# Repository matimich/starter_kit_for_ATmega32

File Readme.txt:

Author:Mateusz Michalski
Program: EAGLE

The aim of the project was to create starter kit for ATmega32.

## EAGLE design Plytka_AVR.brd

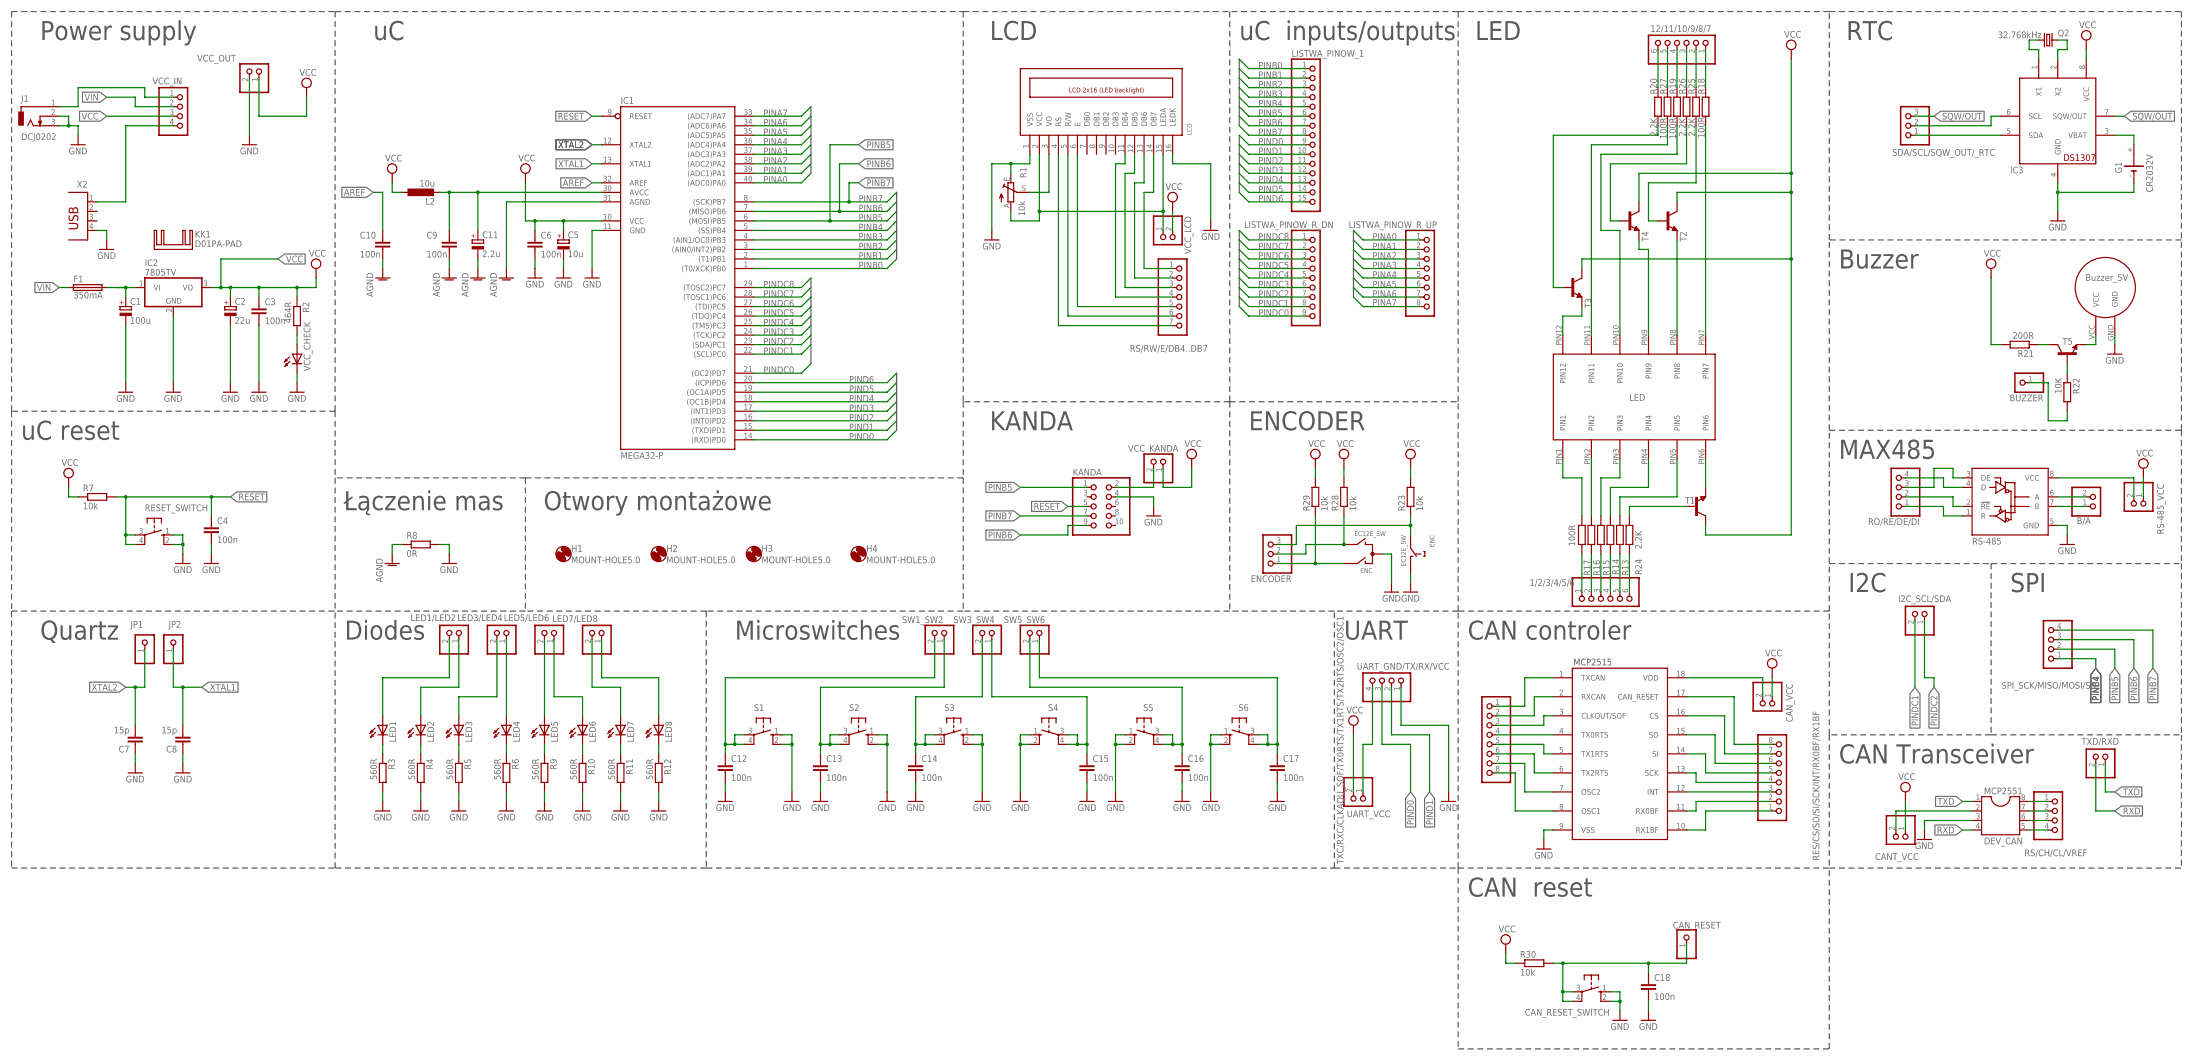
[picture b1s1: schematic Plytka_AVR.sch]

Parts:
1/2/3/4/5/6, 12/11/10/9/8/7: PINHD-1X6; 1X06
B/A: PINHD-1X2; 1X02
BUZZER: PINHD-1X1; 1X01
C1: 100u; E2,5-6
C2: 22u; E2,5-6
C3, C4, C6, C9, C10, C12, C13, C14, C15, C16, C17, C18: 100n; C050-024X044
C5: 10u; E2,5-6
C7, C8: 15p; C050-024X044
C11: 2.2u; E2,5-6
CANT_VCC: PINHD-1X2; 1X02
CAN_RESET: PINHD-1X1; 1X01
CAN_RESET_SWITCH: 10-XX; B3F-10XX
CAN_VCC: PINHD-1X2; 1X02
ENC: EC12E_SW; ALPS_EC12E_SW
ENCODER: PINHD-1X3; 1X03
F1: 350mA; SHK20L
G1: CR2032V
H1, H2, H3, H4: MOUNT-HOLE5.0; 5,0
I2C_SCL/SDA: PINHD-1X2; 1X02
IC1: MEGA32-P; DIL40
IC2: 7805TV; TO220V
IC3: DS1307; DIL08
J1: DCJ0202
JP1, JP2: PINHD-1X1; 1X01
KANDA: PINHD-2X5; 2X05
KK1: D01PA-PAD
L2: 10u; 0204/7
LCD: LCD_2X16_SIL; HY-1602F
LED1, LED2, LED3, LED4, LED5, LED6, LED7, LED8: LED5MM
LED1/LED2, LED3/LED4, LED5/LED6, LED7/LED8: PINHD-1X2; 1X02
LISTWA_PINOW_1: PINHD-1X15; 1X15
LISTWA_PINOW_R_DN: PINHD-1X9; 1X09
LISTWA_PINOW_R_UP: PINHD-1X8MAT8; 1X08
MCP2551: DEV_CAN; DIL08
Q2: 32.768kHz; TC26V
R1: 10k; CA6V
R2: 464R; 0204/7
R3, R4, R5, R6, R9, R10, R11, R12: 560R; 0204/7
R7, R23, R28, R29, R30: 10k; 0204/7
R8: 0R; 0204/7
R13, R14, R15, R16, R17, R18, R19, R27: 100R; 0204/7
R20, R24, R25, R26: 2.2K; 0204/7
R21: 200R; 0204/7
R22: 10K; 0204/7
RES/CS/SO/SI/SCK/INT/RX0BF/RX1BF: PINHD-1X8; 1X08
RESET_SWITCH: 10-XX; B3F-10XX
RO/RE/DE/DI: PINHD-1X4; 1X04
RS-485: RS-485; DIL08
RS-485_VCC: PINHD-1X2; 1X02
RS/CH/CL/VREF: PINHD-1X4; 1X04
RS/RW/E/DB4..DB7: PINHD-1X7MAT_LCD; 1X07
S1, S2, S3, S4, S5, S6: 10-XX; B3F-10XX
SDA/SCL/SQW_OUT/_RTC: PINHD-1X3; 1X03
SPI_SCK/MISO/MOSI/SS: PINHD-1X4; 1X04
SW1_SW2, SW3_SW4, SW5_SW6: PINHD-1X2; 1X02
T1, T2, T3, T4, T5: -NPN-TO92; TO92
TXC/RXC/CLKAOU_SOF/TX0RTS/TX1RTS/TX2RTS/OSC2/OSC1: PINHD-1X8; 1X08
TXD/RXD: PINHD-1X2; 1X02
U$1: LED_MAT; LED_MOJ
U$2: BUZZER_MAT
U$3: MCP2515; DIP18
UART_GND/TX/RX/VCC: PINHD-1X4; 1X04
UART_VCC: PINHD-1X2; 1X02
VCC_CHECK: LED5MM
VCC_IN: PINHD-1X4; 1X04
VCC_KANDA: PINHD-1X2; 1X02
VCC_LCD: PINHD-1X2; 1X02
VCC_OUT: PINHD-1X2; 1X02
X2: PN87520

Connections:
AGND: C9.2, C10.2, C11.-, IC1.31 (AGND), R8.1
AREF: C10.1, IC1.32 (AREF)
DB4: LCD.11 (DB4), RS/RW/E/DB4..DB7.4
DB5: LCD.12 (DB5), RS/RW/E/DB4..DB7.3
DB6: LCD.13 (DB6), RS/RW/E/DB4..DB7.2
DB7: LCD.14 (DB7), RS/RW/E/DB4..DB7.1
E: LCD.6 (E), RS/RW/E/DB4..DB7.5
GND: C1.-, C2.-, C3.2, C4.2, C5.-, C6.2, C7.1, C8.1, C12.2, C13.2, C14.2, C15.2, C16.2, C17.2, C18.2, CAN_RESET_SWITCH.1 (S), CAN_RESET_SWITCH.2 (S1), ENC.C, ENC.D (1), G1.-, IC1.11 (GND), IC2.2 (GND), IC3.4 (GND), J1.2, J1.3, KANDA.4, LCD.1 (VSS), LCD.16 (LEDK), MCP2551.3 (VDD), R1.E, R3.2, R4.2, R5.2, R6.2, R8.2, R9.2, R10.2, R11.2, R12.2, RESET_SWITCH.1 (S), RESET_SWITCH.2 (S1), RS-485.5 (GND), S1.1 (S), S1.2 (S1), S2.1 (S), S2.2 (S1), S3.1 (S), S3.2 (S1), S4.1 (S), S4.2 (S1), S5.1 (S), S5.2 (S1), S6.1 (S), S6.2 (S1), U$2.GND, U$3.9 (VSS), UART_GND/TX/RX/VCC.1, VCC_CHECK.K (C), VCC_OUT.2 (1), X2.4
unnamed: J1.1, VCC_IN.1
unnamed: VCC_IN.4, X2.1
unnamed: T1.1 (E), U$1.PIN6
unnamed: R2.2, VCC_CHECK.A
unnamed: C9.1, C11.+, IC1.30 (AVCC), L2.2
unnamed: MCP2551.8 (RS), RS/CH/CL/VREF.1
unnamed: 12/11/10/9/8/7.6 (1), R20.1
unnamed: 1/2/3/4/5/6.1 (6), R17.2
unnamed: 1/2/3/4/5/6.2 (5), R16.2
unnamed: 1/2/3/4/5/6.3 (4), R15.2
unnamed: 1/2/3/4/5/6.4 (3), R14.2
unnamed: 1/2/3/4/5/6.5 (2), R13.2
unnamed: R17.1, U$1.PIN1
unnamed: R27.1, U$1.PIN11
unnamed: LED1.K (C), R3.1
unnamed: LED1.A, LED1/LED2.2 (1)
unnamed: 12/11/10/9/8/7.4 (3), R19.2
unnamed: R18.1, U$1.PIN7
unnamed: R16.1, U$1.PIN2
unnamed: R15.1, U$1.PIN3
unnamed: R14.1, U$1.PIN4
unnamed: R13.1, U$1.PIN5
unnamed: 12/11/10/9/8/7.1 (6), R18.2
unnamed: 12/11/10/9/8/7.2 (5), R25.1
unnamed: T2.1 (E), U$1.PIN8
unnamed: 1/2/3/4/5/6.6 (1), R24.1
unnamed: LED1/LED2.1 (2), LED2.A
unnamed: LED3.A, LED3/LED4.2 (1)
unnamed: LED5/LED6.1 (2), LED6.A
unnamed: LED5.K (C), R9.1
unnamed: LED2.K (C), R4.1
unnamed: LED6.K (C), R10.1
unnamed: LED3.K (C), R5.1
unnamed: LED7.K (C), R11.1
unnamed: LED4.K (C), R6.1
unnamed: LED8.K (C), R12.1
unnamed: LED5.A, LED5/LED6.2 (1)
unnamed: MCP2551.7 (CANH), RS/CH/CL/VREF.2
unnamed: LED7/LED8.1 (2), LED8.A
unnamed: C18.1, CAN_RESET.1, CAN_RESET_SWITCH.3, CAN_RESET_SWITCH.4 (P1), R30.2
unnamed: LCD.3 (VO), R1.S
unnamed: KANDA.2, VCC_KANDA.2 (1)
unnamed: MCP2551.6 (CANL), RS/CH/CL/VREF.3
unnamed: MCP2551.5 (VREF), RS/CH/CL/VREF.4
unnamed: R24.2, T1.2 (B)
unnamed: R25.2, T2.2 (B)
unnamed: T4.1 (E), U$1.PIN9
unnamed: 12/11/10/9/8/7.3 (4), R26.1
unnamed: IC3.6 (SCL), SDA/SCL/SQW_OUT/_RTC.2
unnamed: R26.2, T4.2 (B)
unnamed: IC3.5 (SDA), SDA/SCL/SQW_OUT/_RTC.1
unnamed: R19.1, U$1.PIN10
unnamed: 12/11/10/9/8/7.5 (2), R27.2
unnamed: IC3.1 (X1), Q2.1
unnamed: R20.2, T3.2 (B)
unnamed: T3.1 (E), U$1.PIN12
unnamed: IC3.2 (X2), Q2.2
unnamed: G1.+, IC3.3 (VBAT)
unnamed: T5.1 (E), U$2.VCC
unnamed: R21.1, T5.3 (C)
unnamed: R22.1, T5.2 (B)
unnamed: BUZZER.1, R22.2
unnamed: RO/RE/DE/DI.4, RS-485.4 (D)
unnamed: RO/RE/DE/DI.3, RS-485.3 (DE)
unnamed: RO/RE/DE/DI.2, RS-485.2 (!RE)
unnamed: RO/RE/DE/DI.1, RS-485.1 (R)
unnamed: B/A.2 (1), RS-485.6 (A)
unnamed: B/A.1 (2), RS-485.7 (B)
unnamed: ENC.B, ENCODER.2, R28.1
unnamed: ENC.A, ENCODER.1, R29.1
unnamed: CAN_VCC.2 (1), U$3.18 (VDD)
unnamed: ENC.E (2), ENCODER.3, R23.1
unnamed: RES/CS/SO/SI/SCK/INT/RX0BF/RX1BF.1 (8), U$3.10 (RX1BF)
unnamed: RES/CS/SO/SI/SCK/INT/RX0BF/RX1BF.2 (7), U$3.11 (RX0BF)
unnamed: RES/CS/SO/SI/SCK/INT/RX0BF/RX1BF.3 (6), U$3.12 (INT)
unnamed: RES/CS/SO/SI/SCK/INT/RX0BF/RX1BF.4 (5), U$3.13 (SCK)
unnamed: RES/CS/SO/SI/SCK/INT/RX0BF/RX1BF.5 (4), U$3.14 (SI)
unnamed: RES/CS/SO/SI/SCK/INT/RX0BF/RX1BF.6 (3), U$3.15 (SO)
unnamed: RES/CS/SO/SI/SCK/INT/RX0BF/RX1BF.7 (2), U$3.16 (CS)
unnamed: RES/CS/SO/SI/SCK/INT/RX0BF/RX1BF.8 (1), U$3.17 (CAN_RESET)
unnamed: TXC/RXC/CLKAOU_SOF/TX0RTS/TX1RTS/TX2RTS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.8 (1), U$3.8 (OSC1)
unnamed: TXC/RXC/CLKAOU_SOF/TX0RTS/TX1RTS/TX2RTS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.7 (2), U$3.7 (OSC2)
unnamed: TXC/RXC/CLKAOU_SOF/TX0RTS/TX1RTS/TX2RTS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.6 (3), U$3.6 (TX2RTS)
unnamed: TXC/RXC/CLKAOU_SOF/TX0RTS/TX1RTS/TX2RTS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.5 (4), U$3.5 (TX1RTS)
unnamed: TXC/RXC/CLKAOU_SOF/TX0RTS/TX1RTS/TX2RTS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.4 (5), U$3.4 (TX0RTS)
unnamed: TXC/RXC/CLKAOU_SOF/TX0RTS/TX1RTS/TX2RTS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.3 (6), U$3.3 (CLKOUT/SOF)
unnamed: TXC/RXC/CLKAOU_SOF/TX0RTS/TX1RTS/TX2RTS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.2 (7), U$3.2 (RXCAN)
unnamed: TXC/RXC/CLKAOU_SOF/TX0RTS/TX1RTS/TX2RTS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.1 (8), U$3.1 (TXCAN)
unnamed: UART_GND/TX/RX/VCC.4, UART_VCC.1 (2)
unnamed: CANT_VCC.2 (1), MCP2551.2 (VSS)
unnamed: C1.+, F1.2A, IC2.1 (VI)
unnamed: RS-485.8 (VCC), RS-485_VCC.2 (1)
unnamed: LED3/LED4.1 (2), LED4.A
unnamed: LED7.A, LED7/LED8.2 (1)
unnamed: LCD.2 (VCC), LCD.15 (LEDA), R1.A, VCC_LCD.1 (2)
PINA0: IC1.40 ((ADC0)PA0), LISTWA_PINOW_R_UP.1
PINA1: IC1.39 ((ADC1)PA1), LISTWA_PINOW_R_UP.2
PINA2: IC1.38 ((ADC2)PA2), LISTWA_PINOW_R_UP.3
PINA3: IC1.37 ((ADC3)PA3), LISTWA_PINOW_R_UP.4
PINA4: IC1.36 ((ADC4)PA4), LISTWA_PINOW_R_UP.5
PINA5: IC1.35 ((ADC5)PA5), LISTWA_PINOW_R_UP.6
PINA6: IC1.34 ((ADC6)PA6), LISTWA_PINOW_R_UP.7
PINA7: IC1.33 ((ADC7)PA7), LISTWA_PINOW_R_UP.8
PINB0: IC1.1 ((T0/XCK)PB0), LISTWA_PINOW_1.1
PINB1: IC1.2 ((T1)PB1), LISTWA_PINOW_1.2
PINB2: IC1.3 ((AIN0/INT2)PB2), LISTWA_PINOW_1.3
PINB3: IC1.4 ((AIN1/OC0)PB3), LISTWA_PINOW_1.4
PINB4: IC1.5 ((SS)PB4), LISTWA_PINOW_1.5, SPI_SCK/MISO/MOSI/SS.1
PINB5: IC1.6 ((MOSI)PB5), KANDA.1, LISTWA_PINOW_1.6, SPI_SCK/MISO/MOSI/SS.2
PINB6: IC1.7 ((MISO)PB6), KANDA.9, LISTWA_PINOW_1.7, SPI_SCK/MISO/MOSI/SS.3
PINB7: IC1.8 ((SCK)PB7), KANDA.7, LISTWA_PINOW_1.8, SPI_SCK/MISO/MOSI/SS.4
PIND0: IC1.14 ((RXD)PD0), LISTWA_PINOW_1.9, UART_GND/TX/RX/VCC.3
PIND1: IC1.15 ((TXD)PD1), LISTWA_PINOW_1.10, UART_GND/TX/RX/VCC.2
PIND2: IC1.16 ((INT0)PD2), LISTWA_PINOW_1.11
PIND3: IC1.17 ((INT1)PD3), LISTWA_PINOW_1.12
PIND4: IC1.18 ((OC1B)PD4), LISTWA_PINOW_1.13
PIND5: IC1.19 ((OC1A)PD5), LISTWA_PINOW_1.14
PIND6: IC1.20 ((ICP)PD6), LISTWA_PINOW_1.15
PINDC0: IC1.21 ((OC2)PD7), LISTWA_PINOW_R_DN.9
PINDC1: I2C_SCL/SDA.2 (1), IC1.22 ((SCL)PC0), LISTWA_PINOW_R_DN.8
PINDC2: I2C_SCL/SDA.1 (2), IC1.23 ((SDA)PC1), LISTWA_PINOW_R_DN.7
PINDC3: IC1.24 ((TCK)PC2), LISTWA_PINOW_R_DN.6
PINDC4: IC1.25 ((TMS)PC3), LISTWA_PINOW_R_DN.5
PINDC5: IC1.26 ((TDO)PC4), LISTWA_PINOW_R_DN.4
PINDC6: IC1.27 ((TDI)PC5), LISTWA_PINOW_R_DN.3
PINDC7: IC1.28 ((TOSC1)PC6), LISTWA_PINOW_R_DN.2
PINDC8: IC1.29 ((TOSC2)PC7), LISTWA_PINOW_R_DN.1
R/W: LCD.5 (R/W), RS/RW/E/DB4..DB7.6
RESET: C4.1, IC1.9 (RESET), KANDA.5, R7.2, RESET_SWITCH.3, RESET_SWITCH.4 (P1)
RS: LCD.4 (RS), RS/RW/E/DB4..DB7.7
RXD: MCP2551.4 (RXD), TXD/RXD.2 (1)
SQW/OUT: IC3.7 (SQW/OUT), SDA/SCL/SQW_OUT/_RTC.3
SWITCH1: C12.1, S1.3, S1.4 (P1), SW1_SW2.2 (1)
SWITCH5: C13.1, S2.3, S2.4 (P1), SW1_SW2.1 (2)
SWITCH6: C14.1, S3.3, S3.4 (P1), SW3_SW4.2 (1)
SWITCH7: C15.1, S4.3, S4.4 (P1), SW3_SW4.1 (2)
SWITCH8: C16.1, S5.3, S5.4 (P1), SW5_SW6.2 (1)
SWITCH9: C17.1, S6.3, S6.4 (P1), SW5_SW6.1 (2)
TXD: MCP2551.1 (TXD), TXD/RXD.1 (2)
VCC: C2.+, C3.1, C5.+, C6.1, CANT_VCC.1 (2), CAN_VCC.1 (2), IC1.10 (VCC), IC2.3 (VO), IC3.8 (VCC), L2.1, R2.1, R7.1, R21.2, R23.2, R28.2, R29.2, R30.1, RS-485_VCC.1 (2), T1.3 (C), T2.3 (C), T3.3 (C), T4.3 (C), UART_VCC.2 (1), VCC_IN.3, VCC_KANDA.1 (2), VCC_LCD.2 (1), VCC_OUT.1 (2)
VIN: F1.1A, VCC_IN.2
XTAL1: C8.2, IC1.13 (XTAL1), JP2.1
XTAL2: C7.2, IC1.12 (XTAL2), JP1.1

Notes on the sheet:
Power supply
uC reset
Quartz
LCD
KANDA
Diodes
Microswitches
uC inputs/outputs
LED
Łączenie mas
Otwory montażowe
UART
SPI
I2C
RTC
Buzzer
MAX485
CAN controler
ENCODER
CAN Transceiver
CAN reset

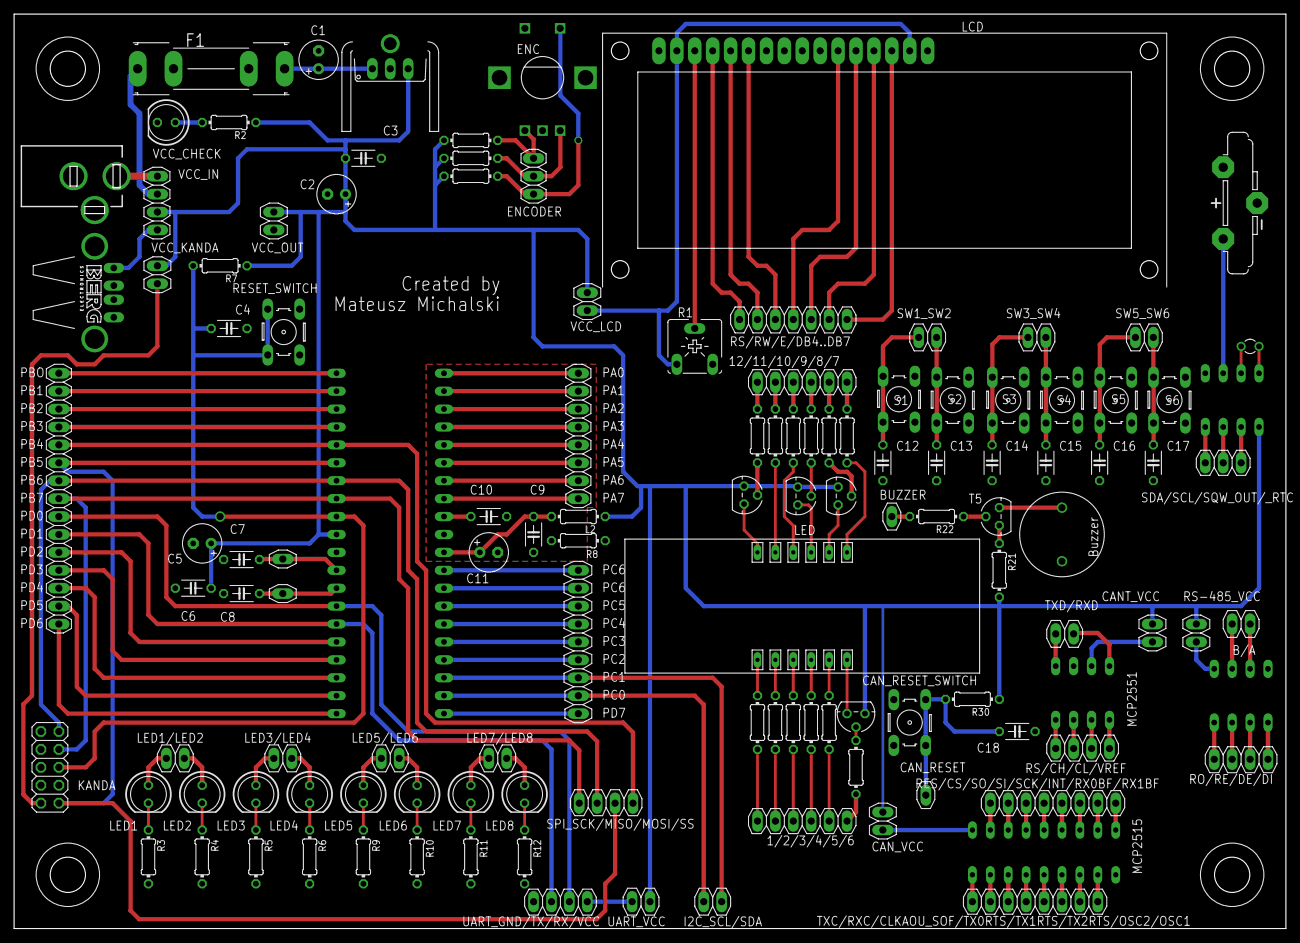
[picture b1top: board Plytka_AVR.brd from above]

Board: 2 copper layers, 180.3 x 129.7 mm, 128 parts (0 on the bottom side), 151 nets.

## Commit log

2018-02-23 My project
